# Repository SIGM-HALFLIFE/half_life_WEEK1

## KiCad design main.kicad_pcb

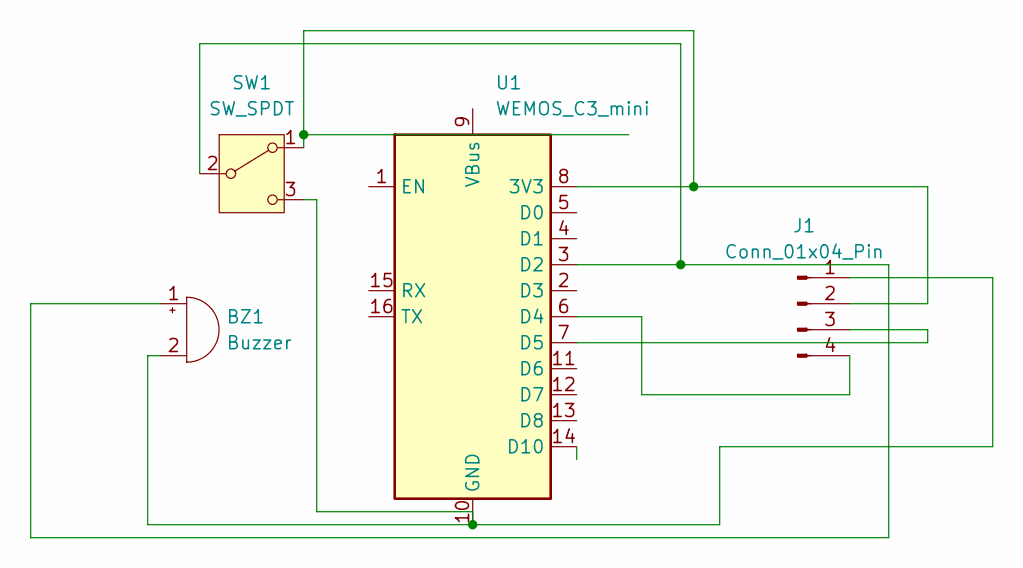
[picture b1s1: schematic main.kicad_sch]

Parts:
BZ1: Buzzer; SOIC-8_3.9x4.9mm_P1.27mm
J1: Conn_01x04_Pin; WEMOS_C3_mini
SW1: SW_SPDT; Nidec_Copal_CAS-120A
U1: WEMOS_C3_mini

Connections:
unnamed: BZ1.1 (+), SW1.2 (B), U1.3 (D2)
unnamed: BZ1.2 (-), J1.1, SW1.3 (C), U1.10 (GND)
unnamed: J1.2, SW1.1 (A), U1.8 (3V3)
unnamed: J1.3, U1.7 (D5)
unnamed: J1.4, U1.6 (D4)

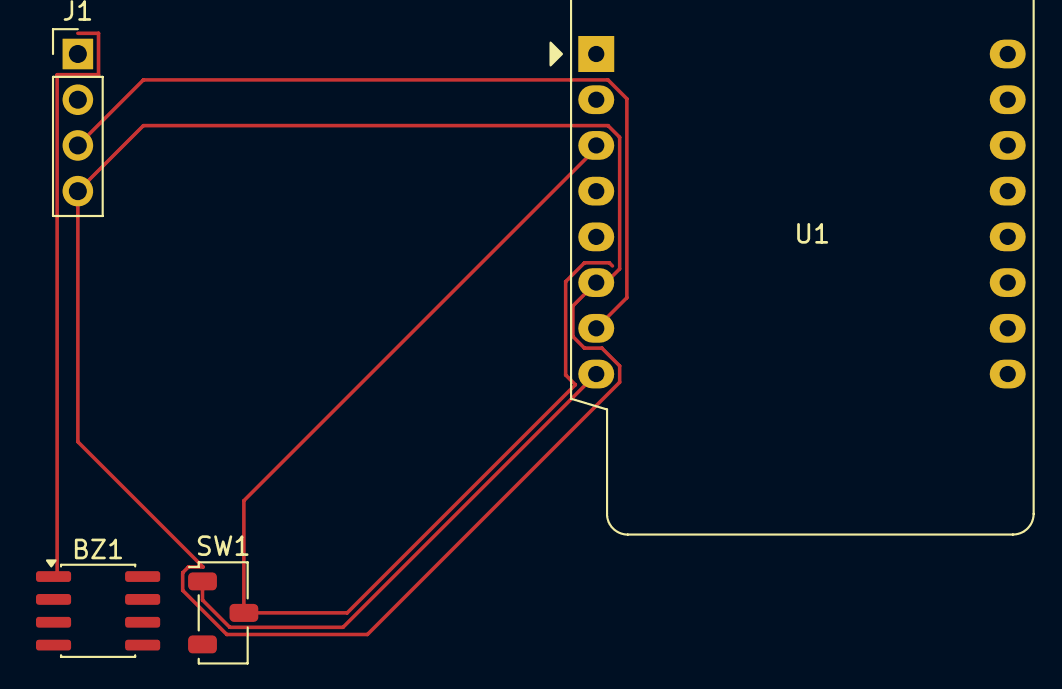
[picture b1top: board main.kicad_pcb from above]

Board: 2 copper layers, 4 parts (0 on the bottom side), 5 nets.
